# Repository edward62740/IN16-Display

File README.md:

# WMNS IN-16

This is an Internet connected nixie tube display (4 x IN-16s) for displaying information (e.g CO2 levels, air quality...). It is designed to be used with [Wireless Mesh Network System](https://github.com/edward62740/Wireless-Mesh-Network-System) or other similar system with a database (InfluxDB, Firebase) to fetch and display information.

This project allows for seamless integration into existing smart home networks for displaying data which users may not want to access using an app/web application (i.e CO2 levels at a glance).

The provided software displays CO2 data on the device, and hosts a webserver to allow for adjustment of input source if necessary (i.e sensor 1/2).

The hardware consists of an ESP32 with GPIO expander, HV power supply, darlington arrays, fan and 4x in-16 tubes. It is based on the hardware from one of my other projects: [Project Nixie](https://github.com/devKarthikRaj/project-nixie "Project Nixie").

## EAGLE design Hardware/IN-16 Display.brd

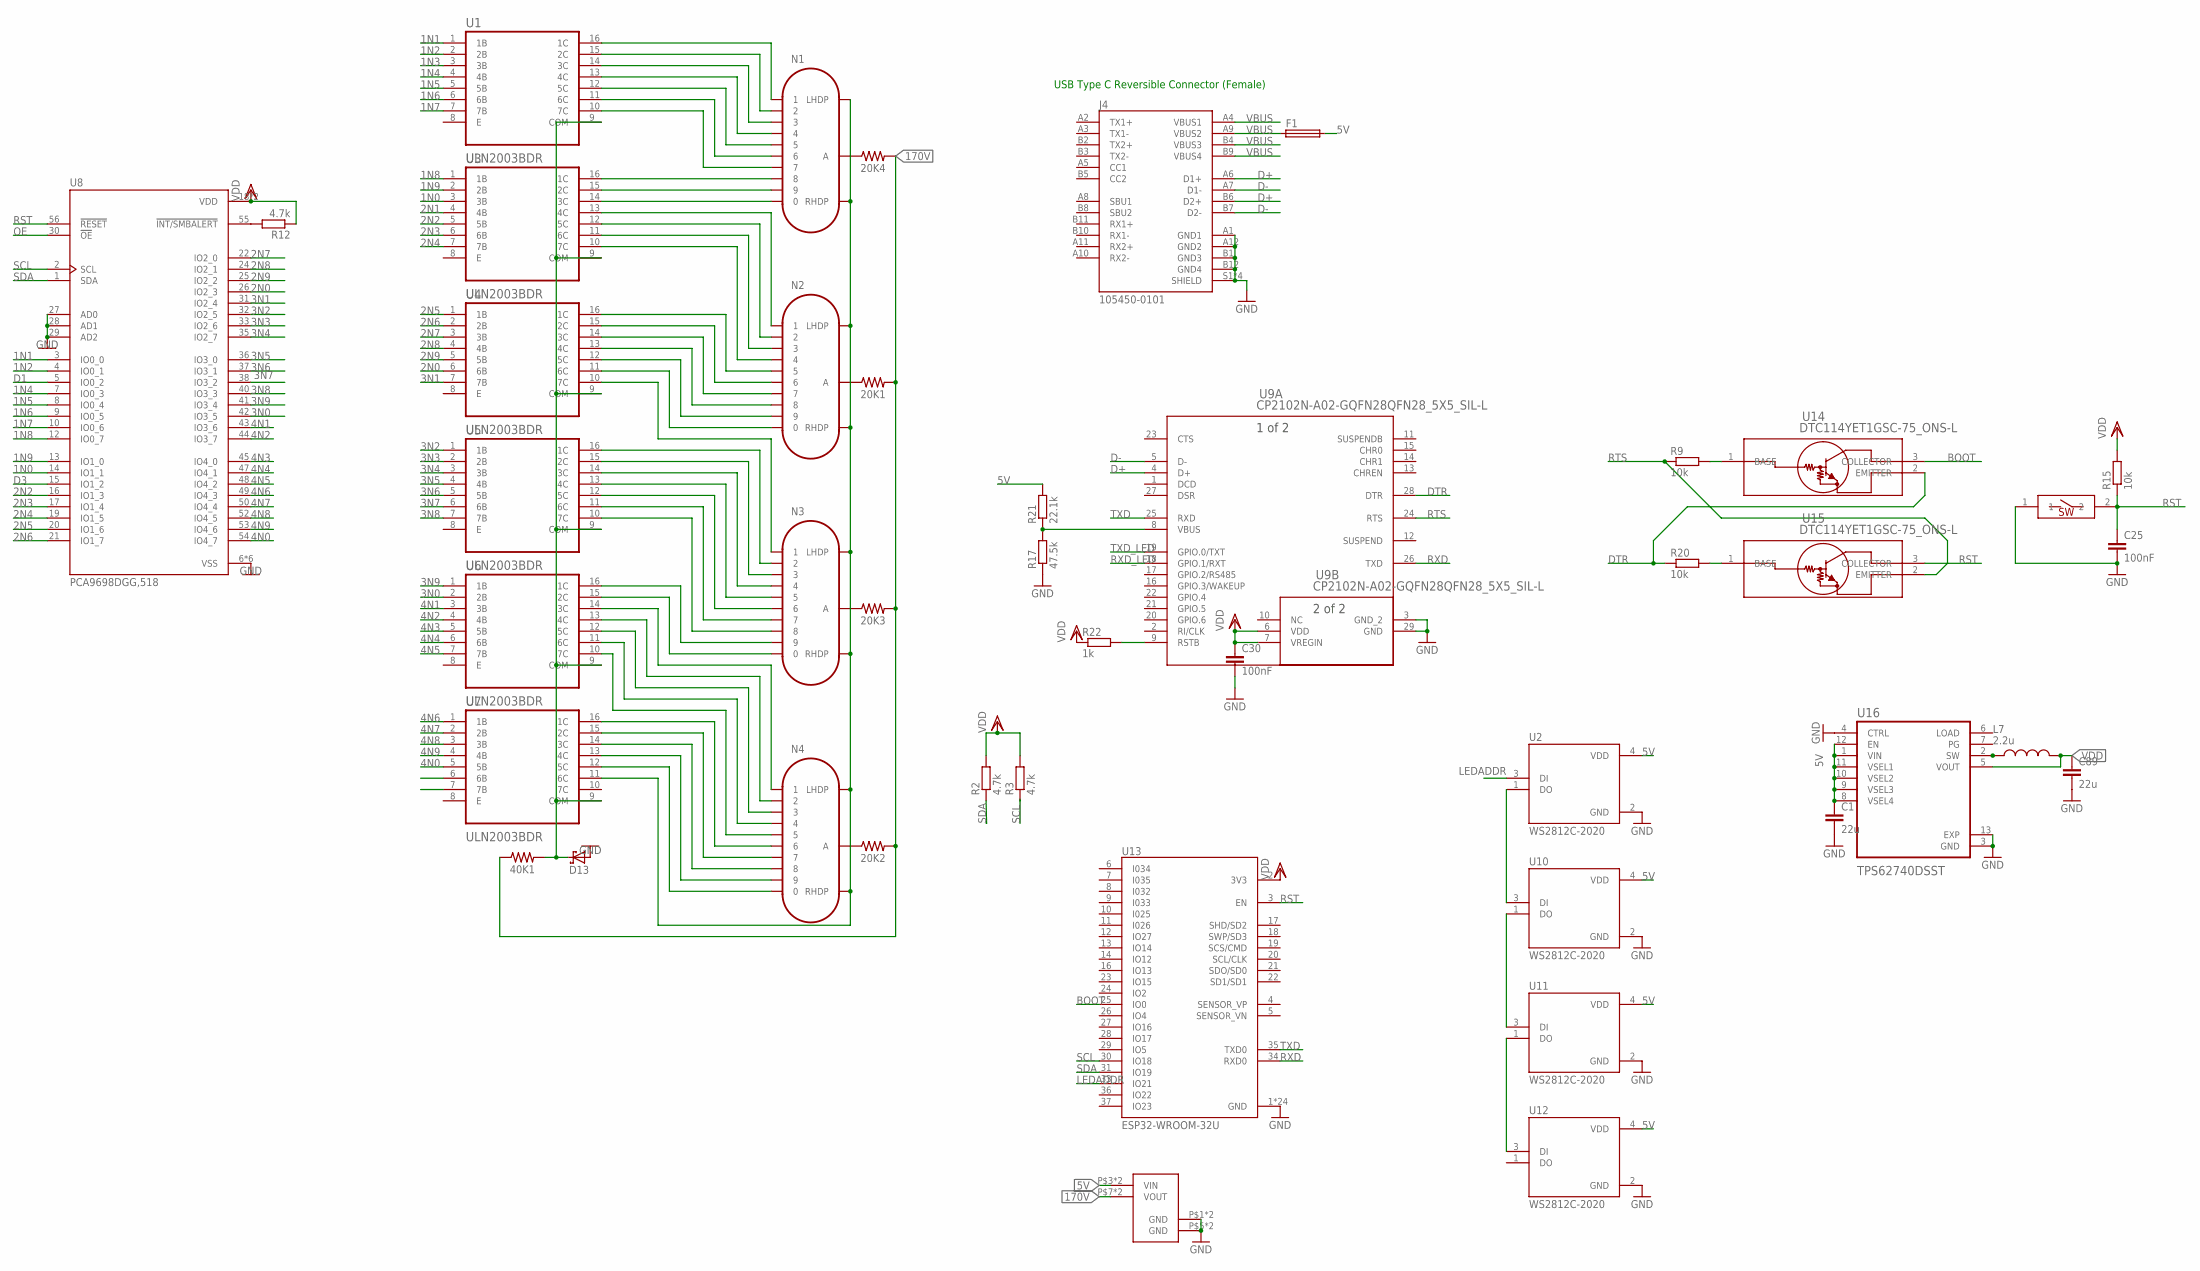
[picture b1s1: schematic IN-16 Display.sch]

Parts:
20K1, 20K2, 20K3, 20K4, 40K1: 0.05; 1210
C1, C89: 22u; C0603R
C25, C30: 100nF; C0402
D13: SCHOTTKY-DIODE; DIODE_SMB
F1: MF-MSMF050-2; 1812
J4: 105450-0101; MOLEX_105450-0101
L7: 2.2u; INDC3225X120N
N1, N2, N3, N4: IN-16
R2, R3, R12: 4.7k; R0402
R9, R15, R20: 10k; R0402
R17: 47.5k; R0402
R21: 22.1k; R0402
R22: 1k; R0402
RESET: SMDSWITCH; RESC4217X170
U1, U3, U4, U5, U6, U7: ULN2003BDR; SOIC127P600X175-16N
U2, U10, U11, U12: WS2812C-2020; LED_WS2812C-2020
U8: PCA9698DGG,518; SOP50P810X120-56N
U9: CP2102N-A02-GQFN28QFN28_5X5_SIL-L; QFN28_5X5_SIL-L
U13: ESP32-WROOM-32U; XCVR_ESP32-WROOM-32U
U14, U15: DTC114YET1GSC-75_ONS-L; SC-75_ONS-L
U16: TPS62740DSST; VREG_LM27762DSSR
U$1: HVPSU

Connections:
1N0: U3.3 (3B), U8.14 (IO1_1)
1N1: U1.1 (1B), U8.3 (IO0_0)
1N2: U1.2 (2B), U8.4 (IO0_1)
1N3: U1.3 (3B)
1N4: U1.4 (4B), U8.7 (IO0_3)
1N5: U1.5 (5B), U8.8 (IO0_4)
1N6: U1.6 (6B), U8.9 (IO0_5)
1N7: U1.7 (7B), U8.10 (IO0_6)
1N8: U3.1 (1B), U8.12 (IO0_7)
1N9: U3.2 (2B), U8.13 (IO1_0)
2N0: U4.6 (6B), U8.26 (IO2_3)
2N1: U3.4 (4B)
2N2: U3.5 (5B), U8.16 (IO1_3)
2N3: U3.6 (6B), U8.17 (IO1_4)
2N4: U3.7 (7B), U8.19 (IO1_5)
2N5: U4.1 (1B), U8.20 (IO1_6)
2N6: U4.2 (2B), U8.21 (IO1_7)
2N7: U4.3 (3B), U8.22 (IO2_0)
2N8: U4.4 (4B), U8.24 (IO2_1)
2N9: U4.5 (5B), U8.25 (IO2_2)
3N0: U6.2 (2B), U8.42 (IO3_5)
3N1: U4.7 (7B), U8.31 (IO2_4)
3N2: U5.1 (1B), U8.32 (IO2_5)
3N3: U5.2 (2B), U8.33 (IO2_6)
3N4: U5.3 (3B), U8.35 (IO2_7)
3N5: U5.4 (4B), U8.36 (IO3_0)
3N6: U5.5 (5B), U8.37 (IO3_1)
3N7: U5.6 (6B), U8.38 (IO3_2)
3N8: U5.7 (7B), U8.40 (IO3_3)
3N9: U6.1 (1B), U8.41 (IO3_4)
4N0: U7.5 (5B), U8.54 (IO4_7)
4N1: U6.3 (3B), U8.43 (IO3_6)
4N2: U6.4 (4B), U8.44 (IO3_7)
4N3: U6.5 (5B), U8.45 (IO4_0)
4N4: U6.6 (6B), U8.47 (IO4_1)
4N5: U6.7 (7B), U8.48 (IO4_2)
4N6: U7.1 (1B), U8.49 (IO4_3)
4N7: U7.2 (2B), U8.50 (IO4_4)
4N8: U7.3 (3B), U8.52 (IO4_5)
4N9: U7.4 (4B), U8.53 (IO4_6)
5V: C1.1, F1.2, R21.2, U2.4 (VDD), U10.4 (VDD), U11.4 (VDD), U12.4 (VDD), U16.1 (VIN), U16.8 (VSEL4), U16.9 (VSEL3), U16.10 (VSEL2), U16.11 (VSEL1), U16.12 (EN), U$1.P$3 (VIN), U$1.P$4 (VIN)
170V: 20K1.2, 20K2.2, 20K3.2, 20K4.2, 40K1.1, U$1.P$7 (VOUT), U$1.P$8 (VOUT)
BOOT: U13.25 (IO0), U14.3 (COLLECTOR)
D1: U8.5 (IO0_2)
D3: U8.15 (IO1_2)
D+: J4.A6 (D1+), J4.B6 (D2+), U9.4 (D+)
D-: J4.A7 (D1-), J4.B7 (D2-), U9.5 (D-)
DTR: R20.1, U9.28 (DTR), U14.2 (EMITTER)
GND: C1.2, C25.2, C30.2, C89.2, D13.A (C), J4.A1 (GND1), J4.A12 (GND2), J4.B1 (GND3), J4.B12 (GND4), J4.S1 (SHIELD), J4.S2 (SHIELD), J4.S3 (SHIELD), J4.S4 (SHIELD), R17.1, RESET.1, U2.2 (GND), U8.6 (VSS), U8.11 (VSS), U8.23 (VSS), U8.27 (AD0), U8.28 (AD1), U8.29 (AD2), U8.34 (VSS), U8.39 (VSS), U8.51 (VSS), U9.3 (GND_2), U9.29 (GND), U10.2 (GND), U11.2 (GND), U12.2 (GND), U13.1 (GND), U13.15 (GND), U13.38 (GND), U13.G.1 (GND), U13.G.2 (GND), U13.G.4 (GND), U13.G.5 (GND), U13.G.6 (GND), U13.G.7 (GND), U13.G.8 (GND), U13.G.9 (GND), U13.G.10 (GND), U13.G.11 (GND), U13.G.12 (GND), U13.G.13 (GND), U13.G.14 (GND), U13.G.15 (GND), U13.G.16 (GND), U13.G.17 (GND), U13.G.18 (GND), U13.G.19 (GND), U13.G.20 (GND), U13.G.21 (GND), U13.G.22 (GND), U16.3 (GND), U16.4 (CTRL), U16.13 (EXP), U$1.P$1 (GND), U$1.P$2 (GND), U$1.P$5 (GND), U$1.P$6 (GND)
LEDADDR: U2.3 (DI), U13.33 (IO21)
unnamed: N1.1, U1.16 (1C)
unnamed: N1.2, U1.15 (2C)
unnamed: N1.3, U1.14 (3C)
unnamed: N1.4, U1.13 (4C)
unnamed: N1.5, U1.12 (5C)
unnamed: N1.6, U1.11 (6C)
unnamed: N1.7, U1.10 (7C)
unnamed: N1.8, U3.16 (1C)
unnamed: N1.9, U3.15 (2C)
unnamed: N1.0, U3.14 (3C)
unnamed: N2.1, U3.13 (4C)
unnamed: N2.2, U3.12 (5C)
unnamed: N2.3, U3.11 (6C)
unnamed: N2.4, U3.10 (7C)
unnamed: N2.5, U4.16 (1C)
unnamed: N2.6, U4.15 (2C)
unnamed: N2.7, U4.14 (3C)
unnamed: N2.8, U4.13 (4C)
unnamed: 20K4.1, N1.A
unnamed: N2.9, U4.12 (5C)
unnamed: N2.0, U4.11 (6C)
unnamed: N3.1, U4.10 (7C)
unnamed: N3.2, U5.16 (1C)
unnamed: N3.3, U5.15 (2C)
unnamed: N3.4, U5.14 (3C)
unnamed: N3.5, U5.13 (4C)
unnamed: N3.6, U5.12 (5C)
unnamed: N3.7, U5.11 (6C)
unnamed: N3.8, U5.10 (7C)
unnamed: N3.9, U6.16 (1C)
unnamed: N3.0, U6.15 (2C)
unnamed: N4.1, U6.14 (3C)
unnamed: N4.2, U6.13 (4C)
unnamed: N4.3, U6.12 (5C)
unnamed: N4.4, U6.11 (6C)
unnamed: N4.5, U6.10 (7C)
unnamed: R20.2, U15.1 (BASE)
unnamed: N4.6, U7.16 (1C)
unnamed: N4.7, U7.15 (2C)
unnamed: N4.8, U7.14 (3C)
unnamed: N4.9, U7.13 (4C)
unnamed: N4.0, U7.12 (5C)
unnamed: 20K1.1, N2.A
unnamed: 20K2.1, N4.A
unnamed: 20K3.1, N3.A
unnamed: R17.2, R21.1, U9.8 (VBUS)
unnamed: R22.2, U9.9 (RSTB)
unnamed: R9.2, U14.1 (BASE)
unnamed: U2.1 (DO), U10.3 (DI)
unnamed: U10.1 (DO), U11.3 (DI)
unnamed: U11.1 (DO), U12.3 (DI)
unnamed: N1.LHDP, N1.RHDP, N2.LHDP, N2.RHDP, N3.LHDP, N3.RHDP, N4.LHDP, N4.RHDP, U7.11 (6C)
unnamed: 40K1.2, D13.C (A), U1.9 (COM), U3.9 (COM), U4.9 (COM), U5.9 (COM), U6.9 (COM), U7.9 (COM)
unnamed: L7.1, U16.2 (SW)
unnamed: R12.2, U8.55 (!INT/SMBALERT)
OE: U8.30 (!OE)
RST: C25.1, R15.1, RESET.2, U8.56 (!RESET), U13.3 (EN), U15.3 (COLLECTOR)
RTS: R9.1, U9.24 (RTS), U15.2 (EMITTER)
RXD: U9.26 (TXD), U13.34 (RXD0)
RXD_LED: U9.18 (GPIO.1/RXT)
SCL: R3.1, U8.2 (SCL), U13.30 (IO18)
SDA: R2.1, U8.1 (SDA), U13.31 (IO19)
TXD: U9.25 (RXD), U13.35 (TXD0)
TXD_LED: U9.19 (GPIO.0/TXT)
VBUS: F1.1, J4.A4 (VBUS1), J4.A9 (VBUS2), J4.B4 (VBUS3), J4.B9 (VBUS4)
VDD: C30.1, C89.1, L7.2, R2.2, R3.2, R12.1, R15.2, R22.1, U8.18 (VDD), U8.46 (VDD), U9.6 (VDD), U9.7 (VREGIN), U13.2 (3V3), U16.5 (VOUT)

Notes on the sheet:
USB Type C Reversible Connector (Female)

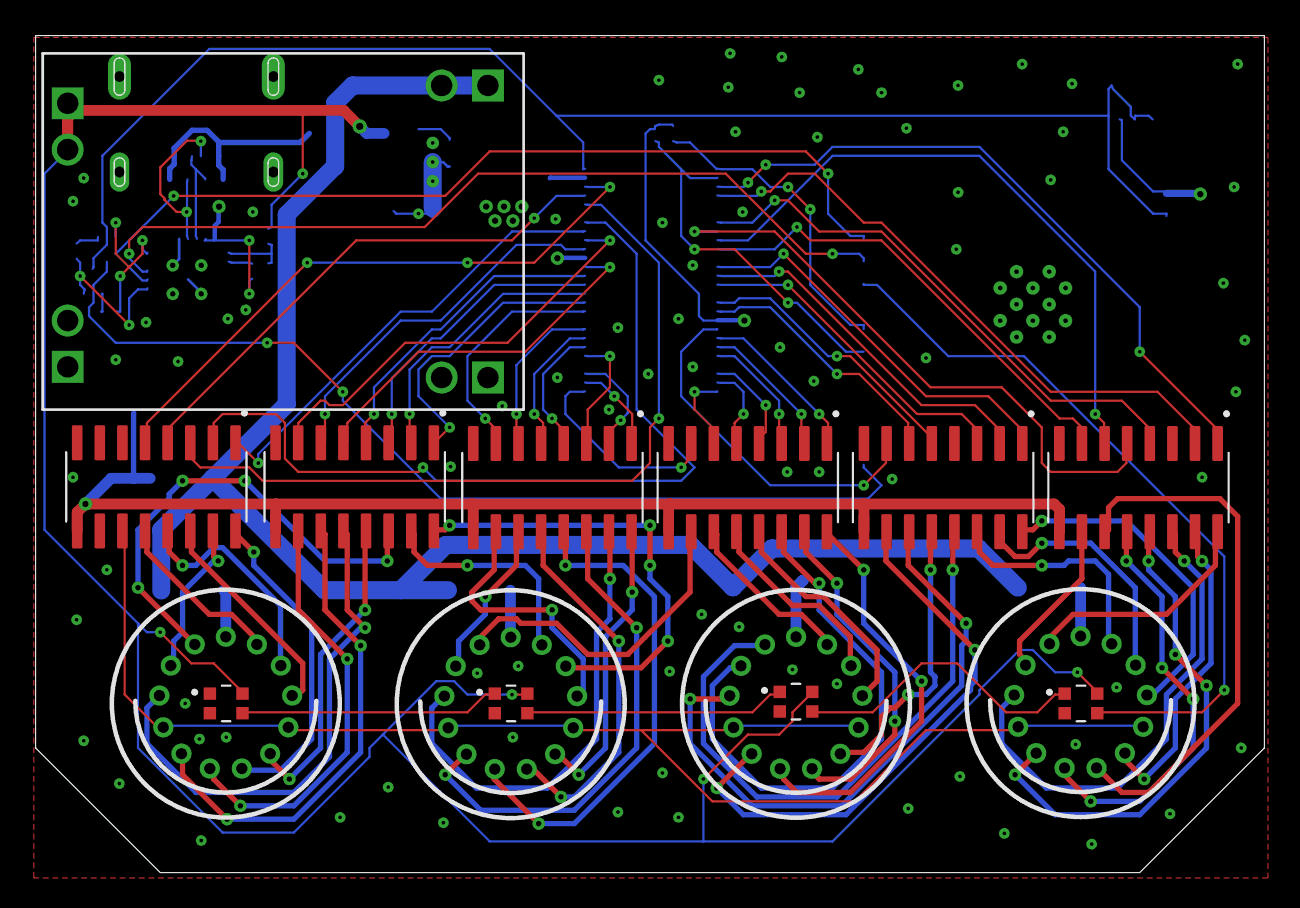
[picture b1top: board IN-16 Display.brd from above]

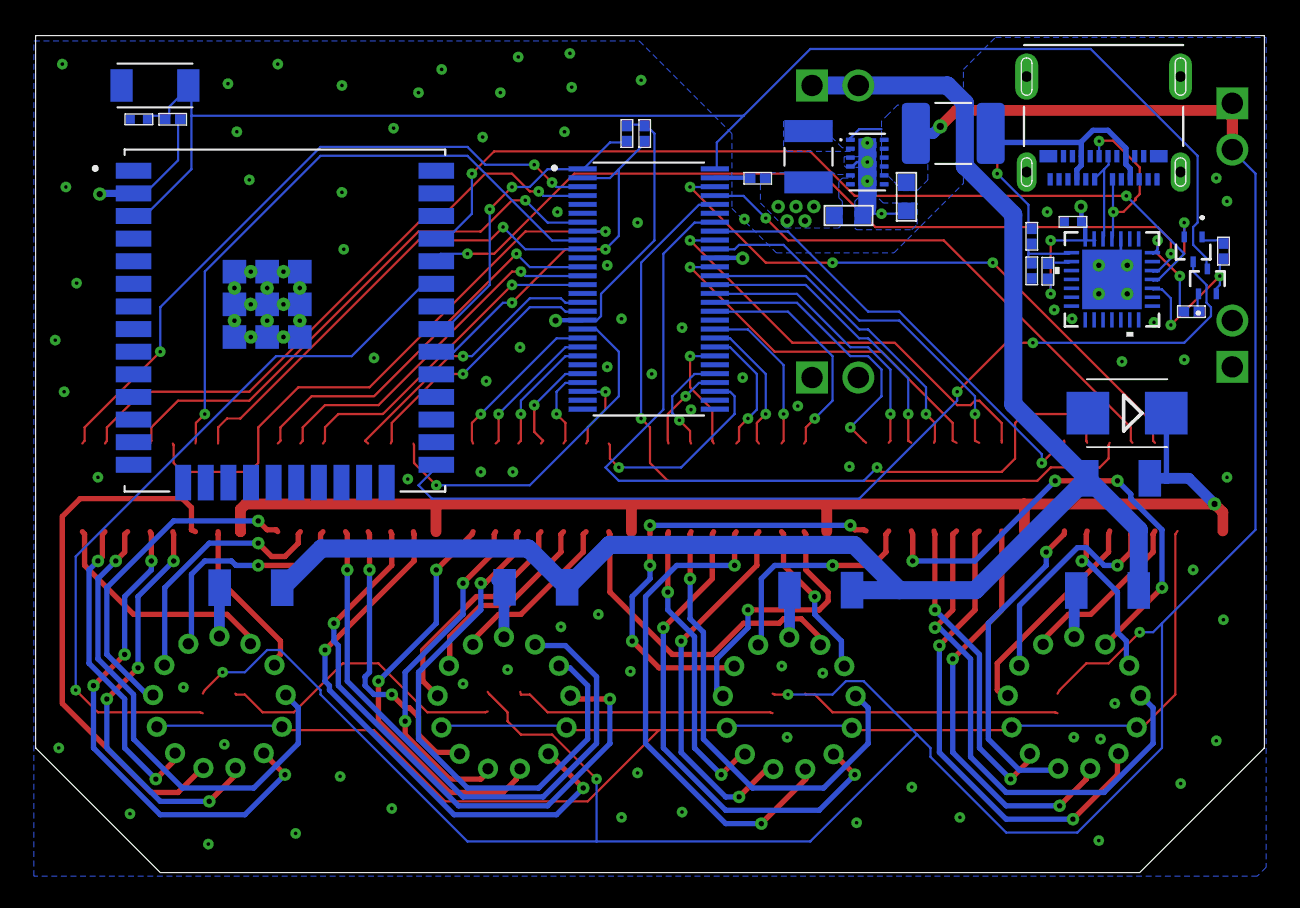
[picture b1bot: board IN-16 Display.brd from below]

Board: 4 copper layers, 69.0 x 47.0 mm, 44 parts (29 on the bottom side), 109 nets.

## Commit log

2022-01-21 Added preliminary
2022-01-30 Added stl

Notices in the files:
parts and their libraries:
SparkFun-Resistors: Licensing: Creative Commons ShareAlike 4.0 International - https://creativecommons.org/licenses/by-sa/4.0
COPYRIGHT: Copyright (C) 2018 Accelerated Designs. All rights reserved
